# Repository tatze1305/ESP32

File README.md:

# ESP32 Entwicklerboard — KiCad Projekt 🕸️

Dies ist das Open-Source-Projekt **Spinne Werkstatt**, erstellt mit [KiCad](https://kicad.org/).  
Es handelt sich um ein Platinen-Design, das frei zur Verfügung steht und für eigene Zwecke verwendet, modifiziert oder weitergegeben werden kann.

---

## 🔧 Inhalt

- `esp32.kicad_sch` — Schaltplan-Datei  
- `esp32.kicad_pcb` — Platinenlayout  
- `gerber/` — Produktionsdaten (Gerber Files)  
- `PDF/` — PDF-Exports für Dokumentation  
- `README.md` — Diese Datei  
- `LICENSE` — Lizenzinformationen (MIT License)

---

## 🚀 Verwendung

Du kannst dieses Projekt:
- verwenden,
- verändern,
- kommerziell oder privat vertreiben,
- als Basis für eigene Entwicklungen nutzen.

Bitte beachte die Lizenzbedingungen in der `LICENSE`-Datei.

---

## 🧑‍💻 Mitmachen

Pull-Requests, Verbesserungen, Bug-Reports oder Ideen sind willkommen!  
Einfach ein Issue öffnen oder forken und loslegen.

---

## 📄 Lizenz

Dieses Projekt steht unter der [MIT License](LICENSE).

> Frei zur Nutzung, Veränderung und Verbreitung — mit Namensnennung.

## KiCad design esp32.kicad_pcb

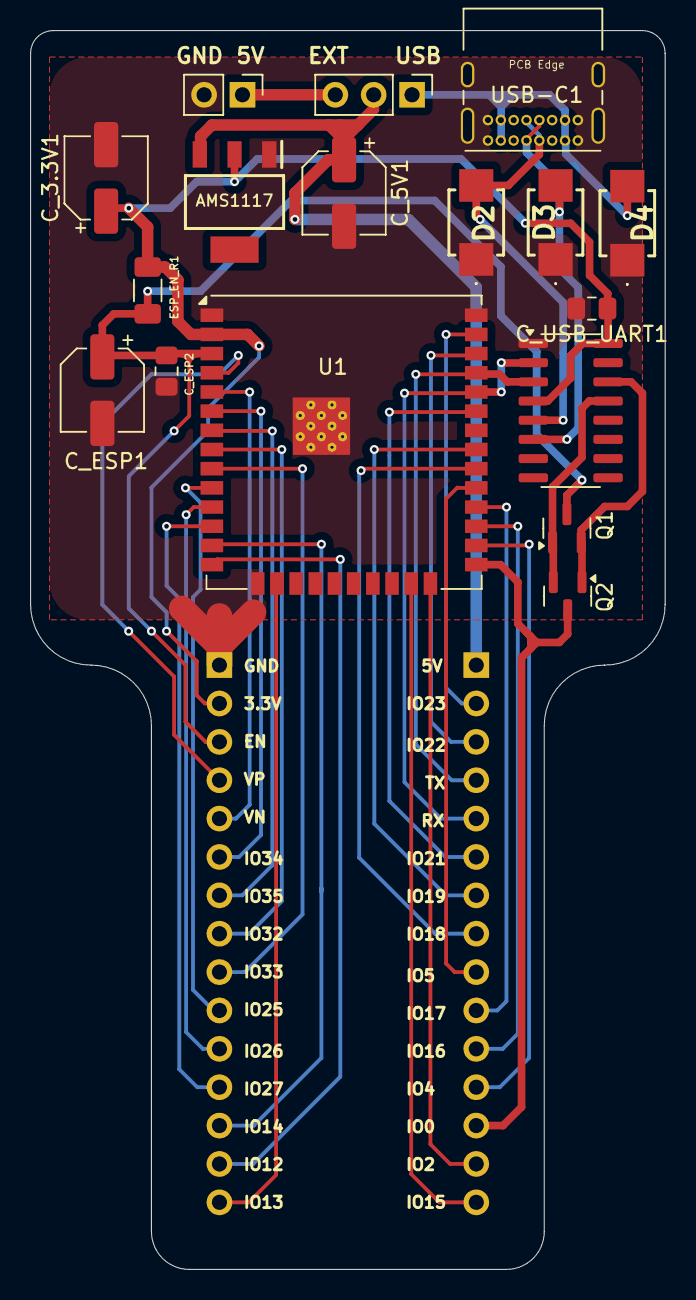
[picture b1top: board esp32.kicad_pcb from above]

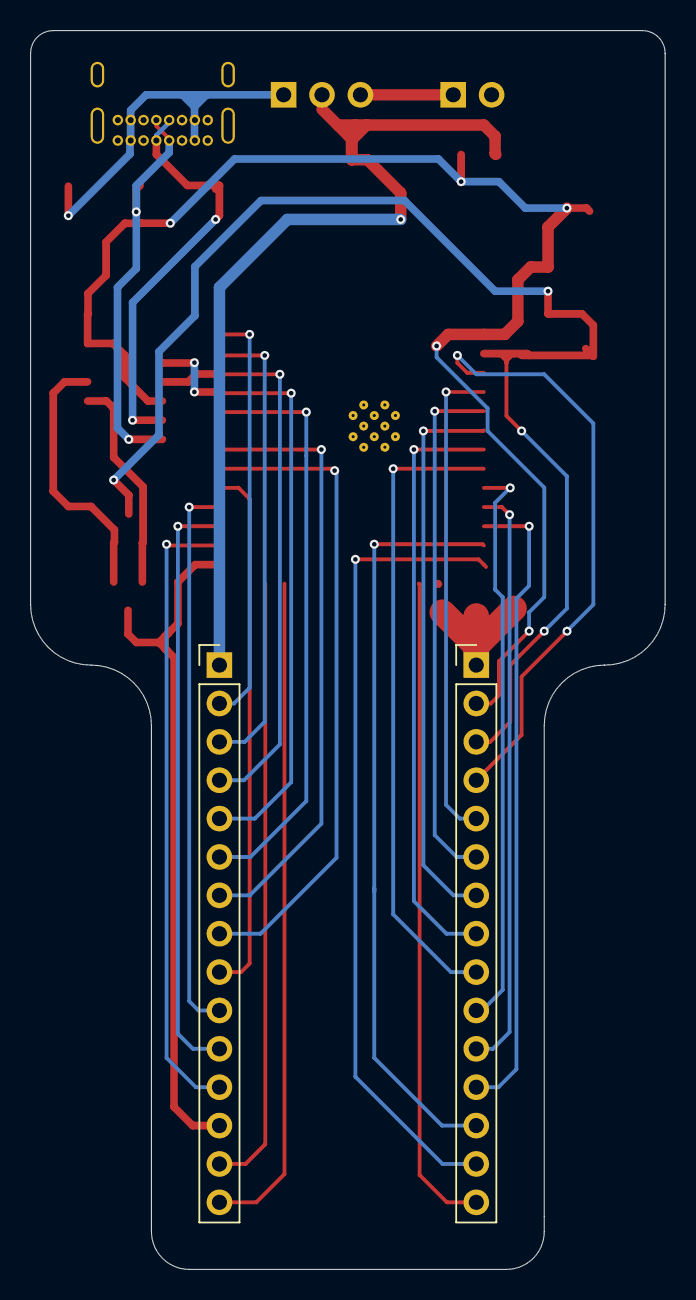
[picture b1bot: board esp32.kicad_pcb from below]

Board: 2 copper layers, 42.0 x 82.0 mm, 19 parts (2 on the bottom side), 36 nets.

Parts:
AMS1117: AMS1117-3.3; SOT230P700X180-4N
C_3.3V1, C_5V1: 1uF; CP_Elec_5x5.4
C_ESP1: 22uF; CP_Elec_5x5.4
C_ESP2: 100nF; C_0805_2012Metric_Pad1.18x1.45mm_HandSolder
C_USB_UART1: 100nF; C_0805_2012Metric_Pad1.18x1.45mm_HandSolder
D2, D3, D4: TPSMB1805CA
ESP_EN_R1: 10k; R_1206_3216Metric_Pad1.30x1.75mm_HandSolder
J1: Conn_01x02_Pin; PinHeader_1x02_P2.54mm_Vertical
J3: Conn_01x03_Pin; PinHeader_1x03_P2.54mm_Vertical
Q1, Q2: BSS138; SOT-23
U1: ESP32-WROOM-32UE
U2: CH340C; SOIC-16_3.9x9.9mm_P1.27mm
USB-C1: USB_C_Receptacle_USB2.0_16P; USB_C_Receptacle_GCT_USB4085
esp_left1: Conn_01x15_Pin; PinHeader_1x15_P2.54mm_Vertical
esp_right1: Conn_01x15_Pin; PinHeader_1x15_P2.54mm_Vertical

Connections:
+3V3: AMS1117.2 (VO), C_3.3V1.1, C_USB_UART1.1, ESP_EN_R1.1, U1.2 (VDD), U2.4 (V3), U2.16 (VCC), esp_left1.2
+5V: AMS1117.3 (VI), C_5V1.1, J3.2, esp_right1.1
D+: D2.2, U2.5 (UD+), USB-C1.A6 (D+), USB-C1.B6 (D+)
D-: D3.2, U2.6 (UD-), USB-C1.A7 (D-), USB-C1.B7 (D-)
ESP32_EN: C_ESP1.1, C_ESP2.1, ESP_EN_R1.2, Q1.3 (D), U1.3 (EN), esp_left1.3
ESP32_IO0: Q2.3 (D), U1.25 (IO0), esp_right1.13
ESP_RX: U1.34 (RXD0/IO3), U2.2 (TXD), esp_right1.5
ESP_TX: U1.35 (TXD0/IO1), U2.3 (RXD), esp_right1.4
GND: AMS1117.1 (GND), C_3.3V1.2, C_5V1.2, C_ESP1.2, C_ESP2.2, C_USB_UART1.2, D2.1, D3.1, D4.1, J1.2, U1.1 (GND), U1.15 (GND), U1.38 (GND), U1.39 (GND), U2.1 (GND), USB-C1.A1 (GND), USB-C1.A12 (GND), USB-C1.B1 (GND), USB-C1.B12 (GND), USB-C1.S1 (SHIELD), esp_left1.1
unnamed: Q1.1 (G), Q2.2 (S), U2.13 (~DTR)
unnamed: Q1.2 (S), Q2.1 (G), U2.14 (~RTS)
VBUS: D4.2, J3.1, USB-C1.A4 (VBUS), USB-C1.A9 (VBUS), USB-C1.B4 (VBUS), USB-C1.B9 (VBUS)
VCC: J1.1, J3.3
pin4: U1.4 (SENSOR_VP), esp_left1.4
pin5: U1.5 (SENSOR_VN), esp_left1.5
pin6: U1.6 (IO34), esp_left1.6
pin7: U1.7 (IO35), esp_left1.7
pin8: U1.8 (IO32), esp_left1.8
pin9: U1.9 (IO33), esp_left1.9
pin10: U1.10 (IO25), esp_left1.10
pin11: U1.11 (IO26), esp_left1.11
pin12: U1.12 (IO27), esp_left1.12
pin13: U1.13 (IO14), esp_left1.13
pin14: U1.14 (IO12), esp_left1.14
pin16: U1.16 (IO13), esp_left1.15
pin23: U1.23 (IO15), esp_right1.15
pin24: U1.24 (IO2), esp_right1.14
pin26: U1.26 (IO4), esp_right1.12
pin27: U1.27 (IO16), esp_right1.11
pin28: U1.28 (IO17), esp_right1.10
pin29: U1.29 (IO5), esp_right1.9
pin30: U1.30 (IO18), esp_right1.8
pin31: U1.31 (IO19), esp_right1.7
pin33: U1.33 (IO21), esp_right1.6
pin36: U1.36 (IO22), esp_right1.3
pin37: U1.37 (IO23), esp_right1.2

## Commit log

2024-12-12 add esp32 wroom
2024-12-12 added esp32 wroom 32UE
2024-12-13 finished first pcb -- ugly
2024-12-30 nearly finished, not perfect but ok
2024-12-30 finished, not that bad
2024-12-30 removed errors, only esp gnd and usb c port ramaining errors, not fixable
2024-12-30 added gerber files
2024-12-30 added gerber
2024-12-30 finished gerber issue
2024-12-31 improved ground plain -- version 1.1.2
2024-12-31 renewed zip
2024-12-31 added IO Names, improved vias
2024-12-31 improved clearences around uart capacitor
2024-12-31 improved clearence around uart capacitor
2024-12-31 changed elko footprints, changed voltage regulator footprint
2024-12-31 finished footprints, all completed -- version 1.1.2
2025-01-01 placed names on silkscreen better
2025-01-01 improved names on silkscreen x2
2025-01-01 added additional USB data protection, not pretty -- version 1.1.3
2025-01-03 elias stinkt
2025-01-10 changed ch340c cap to 0805
2025-01-10 added schematic pdf
2025-01-11 removed usb data protection ic, improvements -- version 1.1.4
2025-04-22 test
2025-04-22 added .gitignore
2025-04-22 Clean: remove now-ignored KiCad temp files
2025-04-22 Improved gitignore
2025-04-22 added pdfs for pcb and schematic --> /PDF, and removed something in .gitignore
2025-04-22 Added Readme and License
2025-04-22 Finished License
2025-04-22 Renamed everything
2025-05-05 removed c at processor
